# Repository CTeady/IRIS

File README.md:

IRIS
====

Integrated Room Sunrise Simulator

Files are to support the building of an alarm clock which ramps on room lighting during alarm condition, turns of lighting or holds it constant during snooze
See progressing build log at http://hackaday.io/project/2291-Integrated-Room-Sunrise-Simulator

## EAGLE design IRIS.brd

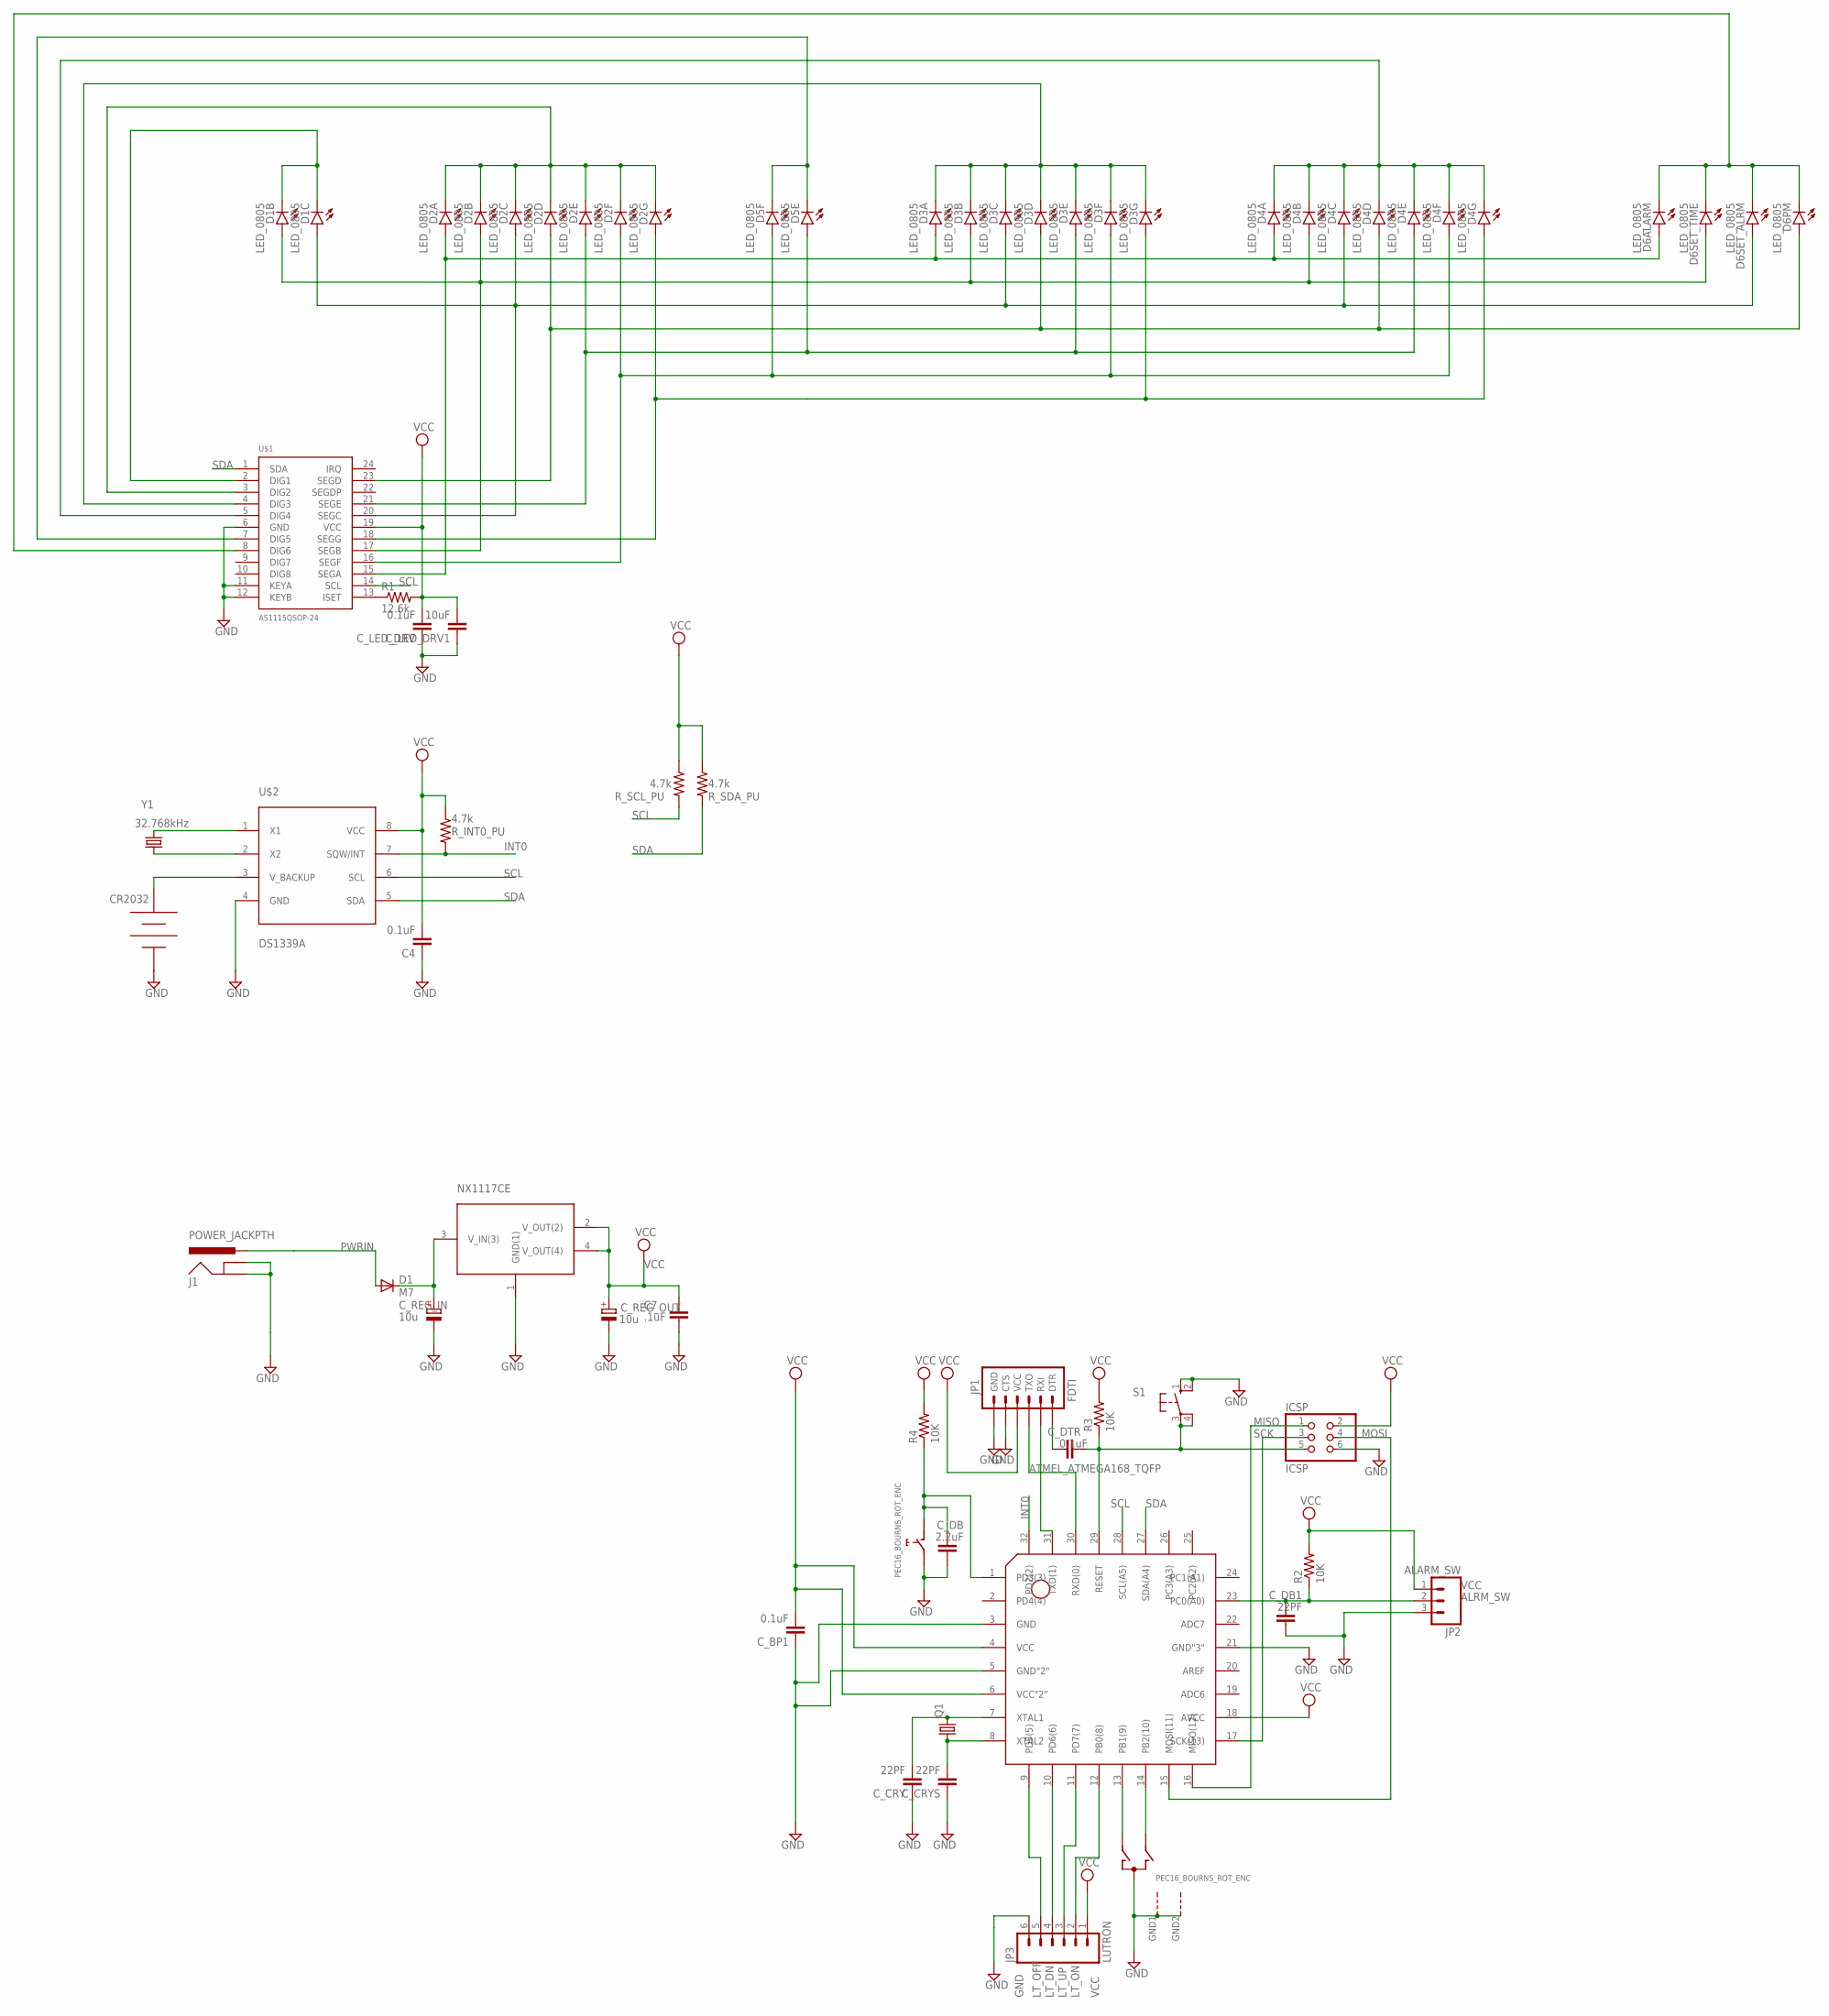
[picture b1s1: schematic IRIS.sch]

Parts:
C4: 0.1uF; 0805
C7: .1uF; C0603-ROUND
C_BP1: 0.1uF; 0805
C_CRY: 22PF; 0805
C_CRYS: 22PF; 0805
C_DB: 2.2uF; 0805
C_DB1: 22PF; 0805
C_DTR: 0.1uF; 0805
C_LED_DRV: 0.1uF; 0805
C_LED_DRV1: 10uF; 0805
C_REG_IN: 10u; PANASONIC_D
C_REG_OUT: 10u; PANASONIC_D
D1: M7; SMB
D1B, D1C, D2A, D2B, D2C, D2D, D2E, D2F, D2G, D3A, D3B, D3C, D3D, D3E, D3F, D3G, D4A, D4B, D4C, D4D, D4E, D4F, D4G, D5E, D5F, D6ALARM, D6PM, D6SET_ALRM, D6SET_TIME: LED_0805
ICSP: ICSP; 2X03
J1: POWER_JACKPTH; POWER_JACK_PTH
JP1: FDTI; 1X06_LONGPADS
JP2: ALARM_SW; 1X03_LONGPADS
JP3: LUTRON; 1X06_LONGPADS
Q1: CRYSTALHC49S; HC49/S
R1: 12.6k; R0805
R2, R3, R4: 10K; R0805
R_INT0_PU: 4.7k; R0805
R_SCL_PU: 4.7k; R0805
R_SDA_PU: 4.7k; R0805
S1: 10-XX; B3F-10XX
U$1: AS1115QSOP-24; SSOP24
U$2: DS1339A; 8_USOP
U$3: CR2032
U$4: PEC16_BOURNS_ROT_ENC; ENCODER_ROTARY
U$5: ATMEL_ATMEGA168_TQFP; TQFP_32_ATMEGA168
U$6: NX1117CE; LINEAR_REG_SOT223
Y1: 32.768kHz; CRYSTAL-32KHZ-SMD

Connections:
ALRM_SW: C_DB1.2, JP2.2, R2.1, U$5.23 (PC0(A0))
D6TIME: D6ALARM.C, D6PM.C, D6SET_ALRM.C, D6SET_TIME.C, U$1.8 (DIG6)
DIGIT1: D1B.C, D1C.C, U$1.2 (DIG1)
DIGIT2: D2A.C, D2B.C, D2C.C, D2D.C, D2E.C, D2F.C, D2G.C, U$1.3 (DIG2)
DIGIT3: D3A.C, D3B.C, D3C.C, D3D.C, D3E.C, D3F.C, D3G.C, U$1.4 (DIG3)
DIGIT4: D4A.C, D4B.C, D4C.C, D4D.C, D4E.C, D4F.C, D4G.C, U$1.5 (DIG4)
DIGIT5: D5E.C, D5F.C, U$1.7 (DIG5)
GND: C4.1, C7.1, C_BP1.1, C_CRY.1, C_CRYS.1, C_DB.1, C_DB1.1, C_LED_DRV.1, C_LED_DRV1.1, C_REG_IN.-, C_REG_OUT.-, ICSP.6, J1.GND, J1.GNDBREAK, JP1.5 (CTS), JP1.6 (GND), JP2.3, JP3.6, S1.1 (S), S1.2 (S1), U$1.6 (GND), U$1.11 (KEYA), U$1.12 (KEYB), U$2.4 (GND), U$3.GND, U$4.C, U$4.E (2), U$4.GND1 (G), U$4.GND2 (G), U$5.3 (GND), U$5.5 (GND"2"), U$5.21 (GND"3"), U$6.1 (GND(1))
INT0: R_INT0_PU.2, U$2.7 (SQW/INT), U$5.32 (PD2(2))
LT_DN: JP3.4, U$5.10 (PD6(6))
LT_OFF: JP3.5, U$5.9 (PD5(5))
LT_ON: JP3.2, U$5.12 (PB0(8))
LT_UP: JP3.3, U$5.11 (PD7(7))
MISO: ICSP.1, U$5.16 (MISO(12))
MOSI: ICSP.4, U$5.15 (MOSI(11))
unnamed: D1B.A, D2B.A, D3B.A, D4B.A, D6SET_TIME.A, U$1.17 (SEGB)
unnamed: D1C.A, D2C.A, D3C.A, D4C.A, D6SET_ALRM.A, U$1.20 (SEGC)
unnamed: U$2.2 (X2), Y1.X1 (1)
unnamed: U$2.1 (X1), Y1.X2 (2)
unnamed: D2A.A, D3A.A, D4A.A, D6ALARM.A, U$1.15 (SEGA)
unnamed: C_DB.2, R4.1, U$4.D (1), U$5.1 (PD3(3))
unnamed: D2D.A, D3D.A, D4D.A, D6PM.A, U$1.23 (SEGD)
unnamed: D2E.A, D3E.A, D4E.A, D5E.A, U$1.21 (SEGE)
unnamed: D2F.A, D3F.A, D4F.A, D5F.A, U$1.16 (SEGF)
unnamed: D2G.A, D3G.A, D4G.A, U$1.18 (SEGG)
unnamed: JP1.2 (RXI), U$5.31 (TXD(1))
unnamed: R1.1, U$1.13 (ISET)
unnamed: JP1.3 (TXO), U$5.30 (RXD(0))
unnamed: C_DTR.2, JP1.1 (DTR)
unnamed: U$4.A, U$5.13 (PB1(9))
unnamed: U$4.B, U$5.14 (PB2(10))
unnamed: C_CRY.2, Q1.2, U$5.7 (XTAL1)
unnamed: C_CRYS.2, Q1.1, U$5.8 (XTAL2)
PWRIN: D1.A, J1.PWR
RESET: C_DTR.1, ICSP.5, R3.1, S1.3, S1.4 (P1), U$5.29 (RESET)
SCK: ICSP.3, U$5.17 (SCK(13))
SCL: R_SCL_PU.2, U$1.14 (SCL), U$2.6 (SCL), U$5.28 (SCL(A5))
SDA: R_SDA_PU.2, U$1.1 (SDA), U$2.5 (SDA), U$5.27 (SDA(A4))
V+: U$2.3 (V_BACKUP), U$3.V+
VCC: C4.2, C7.2, C_BP1.2, C_LED_DRV.2, C_LED_DRV1.2, C_REG_OUT.+, ICSP.2, JP1.4 (VCC), JP2.1, JP3.1, R1.2, R2.2, R3.2, R4.2, R_INT0_PU.1, R_SCL_PU.1, R_SDA_PU.1, U$1.19 (VCC), U$2.8 (VCC), U$5.4 (VCC), U$5.6 (VCC"2"), U$5.18 (AVCC), U$6.2 (V_OUT(2)), U$6.4 (V_OUT(4))
V_IN(3): C_REG_IN.+, D1.C, U$6.3 (V_IN(3))

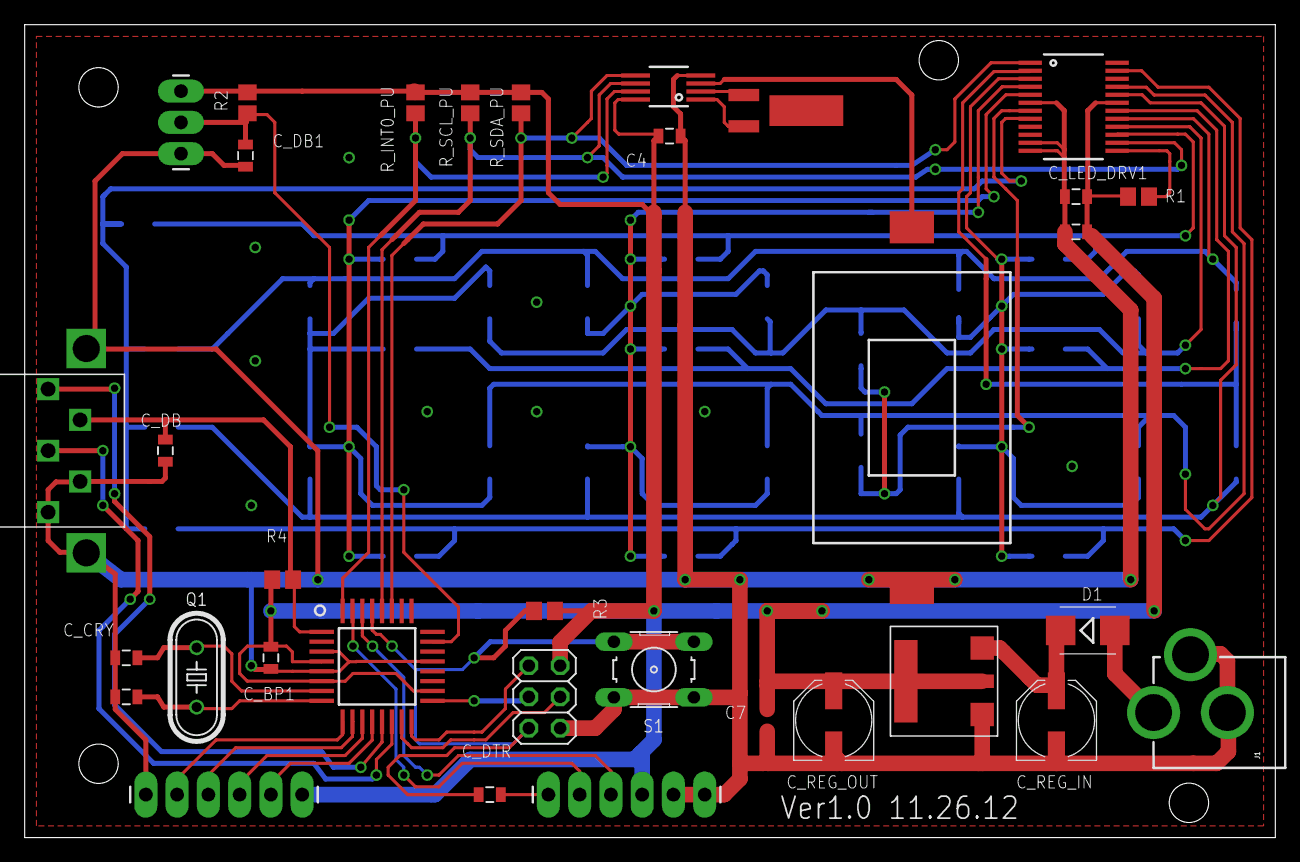
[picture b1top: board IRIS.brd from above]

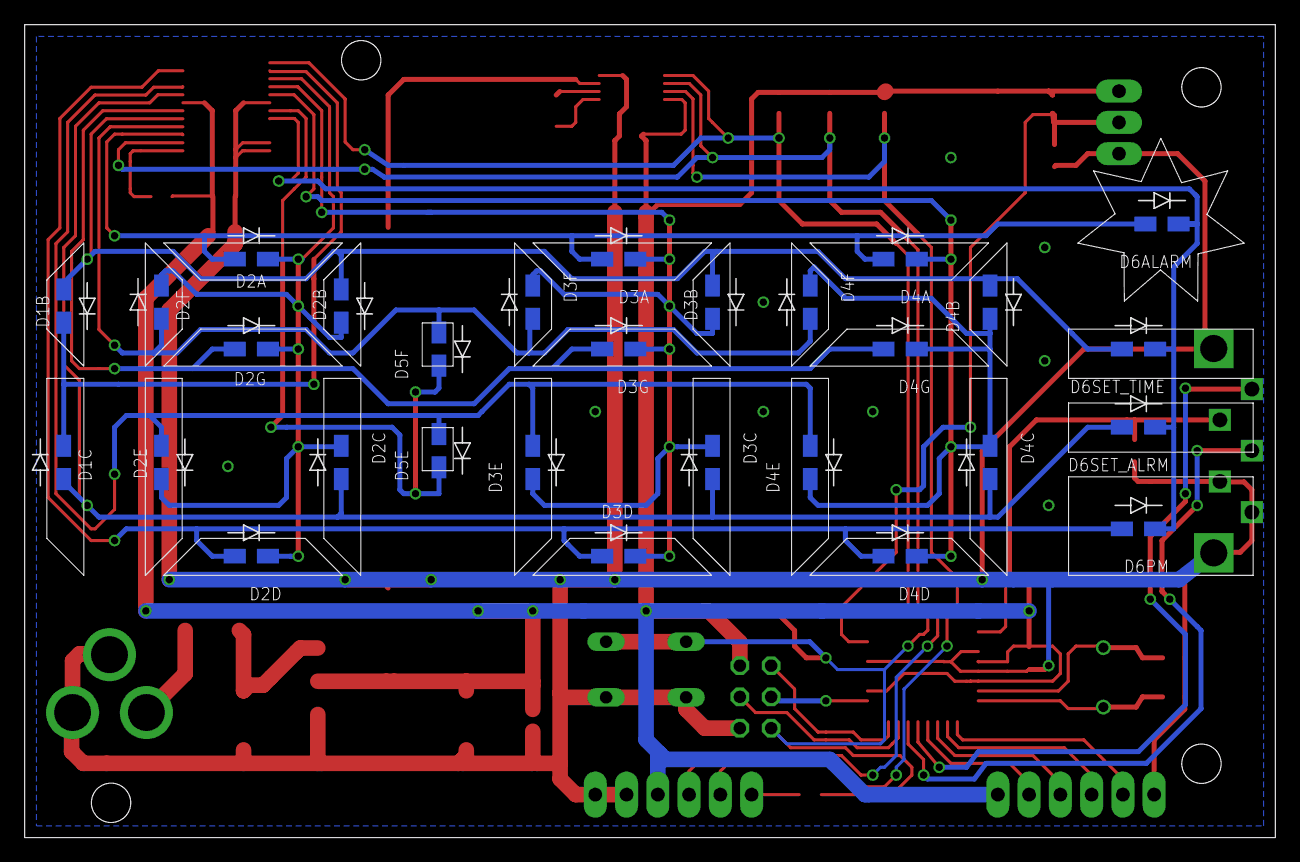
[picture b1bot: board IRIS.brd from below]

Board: 2 copper layers, 101.6 x 66.0 mm, 63 parts (29 on the bottom side), 41 nets.

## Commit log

2014-08-06 :circus_tent: Added .gitattributes & .gitignore files
2014-08-06 IRIS_Master
    IRIS Eagle Schematic & Board files, PDF Schematic, Arduino code, BOM
2014-08-06 IRIS_Plastic
    Front and Rear face of project
2014-08-17 WirelessAnalysis
    and general organization

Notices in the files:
parts and their libraries:
SparkFun-FreqCtrl: Licensing: CC v3.0 Share-Alike You are welcome to use this library for commercial purposes.
